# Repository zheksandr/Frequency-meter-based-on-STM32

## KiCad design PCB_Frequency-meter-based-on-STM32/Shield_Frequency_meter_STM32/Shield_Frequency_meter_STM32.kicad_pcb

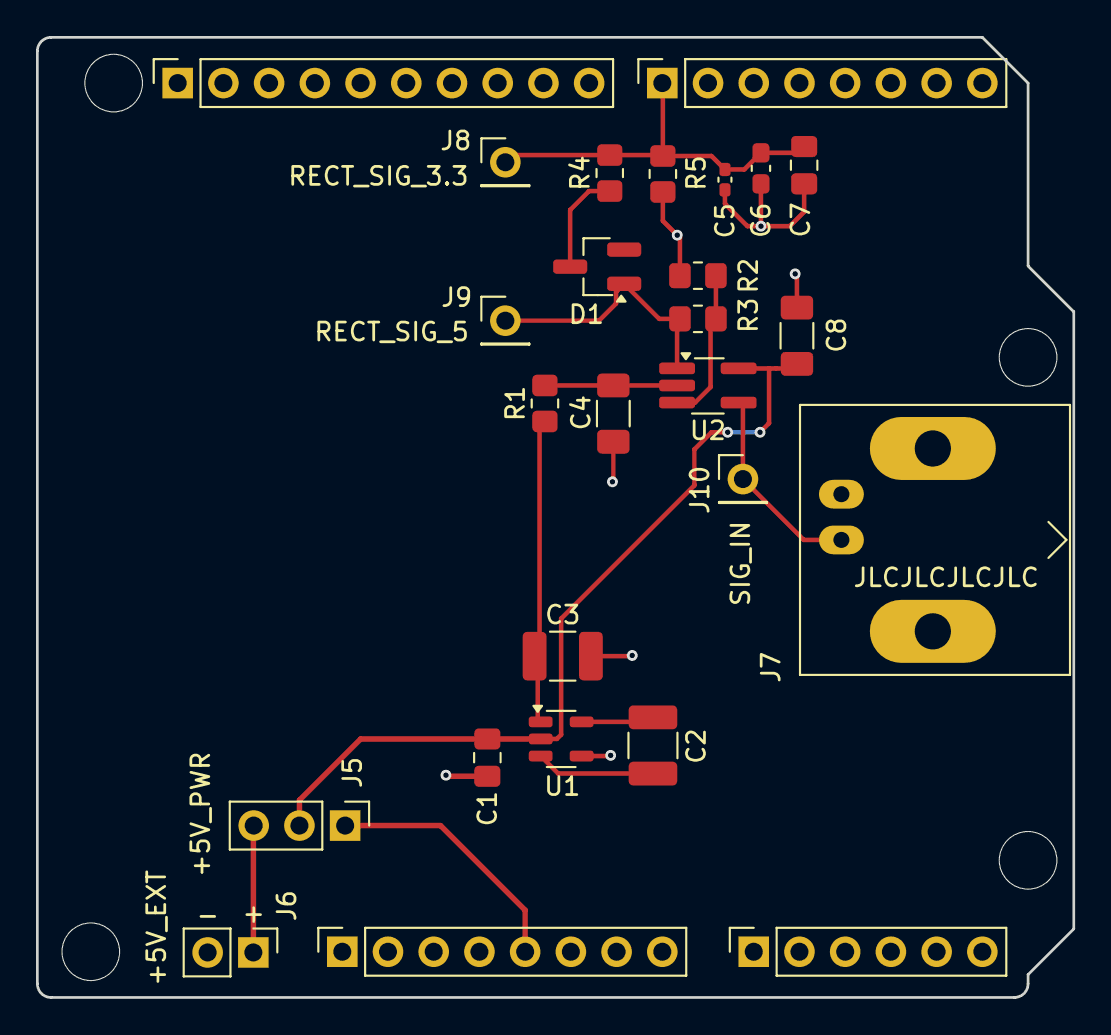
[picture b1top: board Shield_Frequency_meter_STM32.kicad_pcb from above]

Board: 2 copper layers, 57.6 x 53.3 mm, 30 parts (0 on the bottom side), 15 nets.

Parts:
C1: 1uF; C_0805_2012Metric_Pad1.18x1.45mm_HandSolder
C2, C3: 10uF; C_1210_3225Metric_Pad1.33x2.70mm_HandSolder
C4: 0.47uF; C_1206_3216Metric_Pad1.33x1.80mm_HandSolder
C5: 10pF; C_0402_1005Metric_Pad0.74x0.62mm_HandSolder
C6: 22p; C_0603_1608Metric_Pad1.08x0.95mm_HandSolder
C7: 47p; C_0805_2012Metric_Pad1.18x1.45mm_HandSolder
C8: 0.1uF; C_1206_3216Metric_Pad1.33x1.80mm_HandSolder
D1: BAS70-00; SOT-23_Handsoldering
J1: Power; PinSocket_1x08_P2.54mm_Vertical
J2: Digital/PWM; PinSocket_1x10_P2.54mm_Vertical
J3: Analog; PinSocket_1x06_P2.54mm_Vertical
J4: Digital/PWM; PinSocket_1x08_P2.54mm_Vertical
J5: +5V_PWR; PinHeader_1x03_P2.54mm_Vertical
J6: +5V_EXT; PinHeader_1x02_P2.54mm_Vertical
J7: Conn_Coaxial; BNC_Amphenol_B6252HB-NPP3G-50_Horizontal
J8, J9, J10: Conn_01x01; PinHeader_1x01_P2.54mm_Vertical
MH1, MH2, MH3, MH4: MountingHole_3.2mm
R1: 22; R_0805_2012Metric_Pad1.20x1.40mm_HandSolder
R2: 10k; R_0805_2012Metric_Pad1.20x1.40mm_HandSolder
R3: 91k; R_0805_2012Metric_Pad1.20x1.40mm_HandSolder
R4: 20k; R_0805_2012Metric_Pad1.20x1.40mm_HandSolder
R5: 62k; R_0805_2012Metric_Pad1.20x1.40mm_HandSolder
U1: TPS60401DBV; SOT-23-5
U2: OPA210; TSOT-23-5_HandSoldering

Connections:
+5V: C1.1, C8.1, J5.2, U1.2 (IN), U2.5 (V+)
-5V: C4.1, R1.2, U2.2 (V-)
/7: C5.1, C6.1, C7.1, J4.1, J8.1, R4.2, R5.1
/+5V_EXT: J5.3, J6.1
/+5V_STM: J1.5, J5.1
/SCL/A5: J2.1, J3.6
/SDA/A4: J2.2, J3.5
/SIG_IN: J7.1 (In), J10.1, U2.4 (-In)
GND: C1.2, C3.2, C4.2, C5.2, C6.2, C7.2, C8.2, J1.6, J1.7, J2.4, J6.2, J7.2 (Ext), R2.2, R5.2, U1.4 (GND)
unnamed: D1.3, R4.1
unnamed: D1.1, J9.1, R3.1, U2.1 (Out)
unnamed: C2.1, U1.5 (C_{FLY+})
unnamed: C2.2, U1.3 (C_{FLY-})
unnamed: C3.1, R1.1, U1.1 (OUT)
unnamed: R2.1, R3.2, U2.3 (+In)

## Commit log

2024-06-21 The initial template with working LCD screen
2024-06-21 First working version
2024-10-14 The way measurements are taken was changed. Basic processing was added. Code for square wave generator was added
2024-12-01 Added KiCAD PCB project - Arduino Shield Frequency meter
2024-12-06 final PCB update
2024-12-09 small fix
2024-12-17 1) Restructure of project 2) Added communication with PC via USB with FTDI 3) Added crystal oscillator
2024-12-25 New method frequency measurement added
2025-01-05 Commit before modification of direct counting method
2025-01-08 modification of the code of direct counting method
2025-01-11 Final version
